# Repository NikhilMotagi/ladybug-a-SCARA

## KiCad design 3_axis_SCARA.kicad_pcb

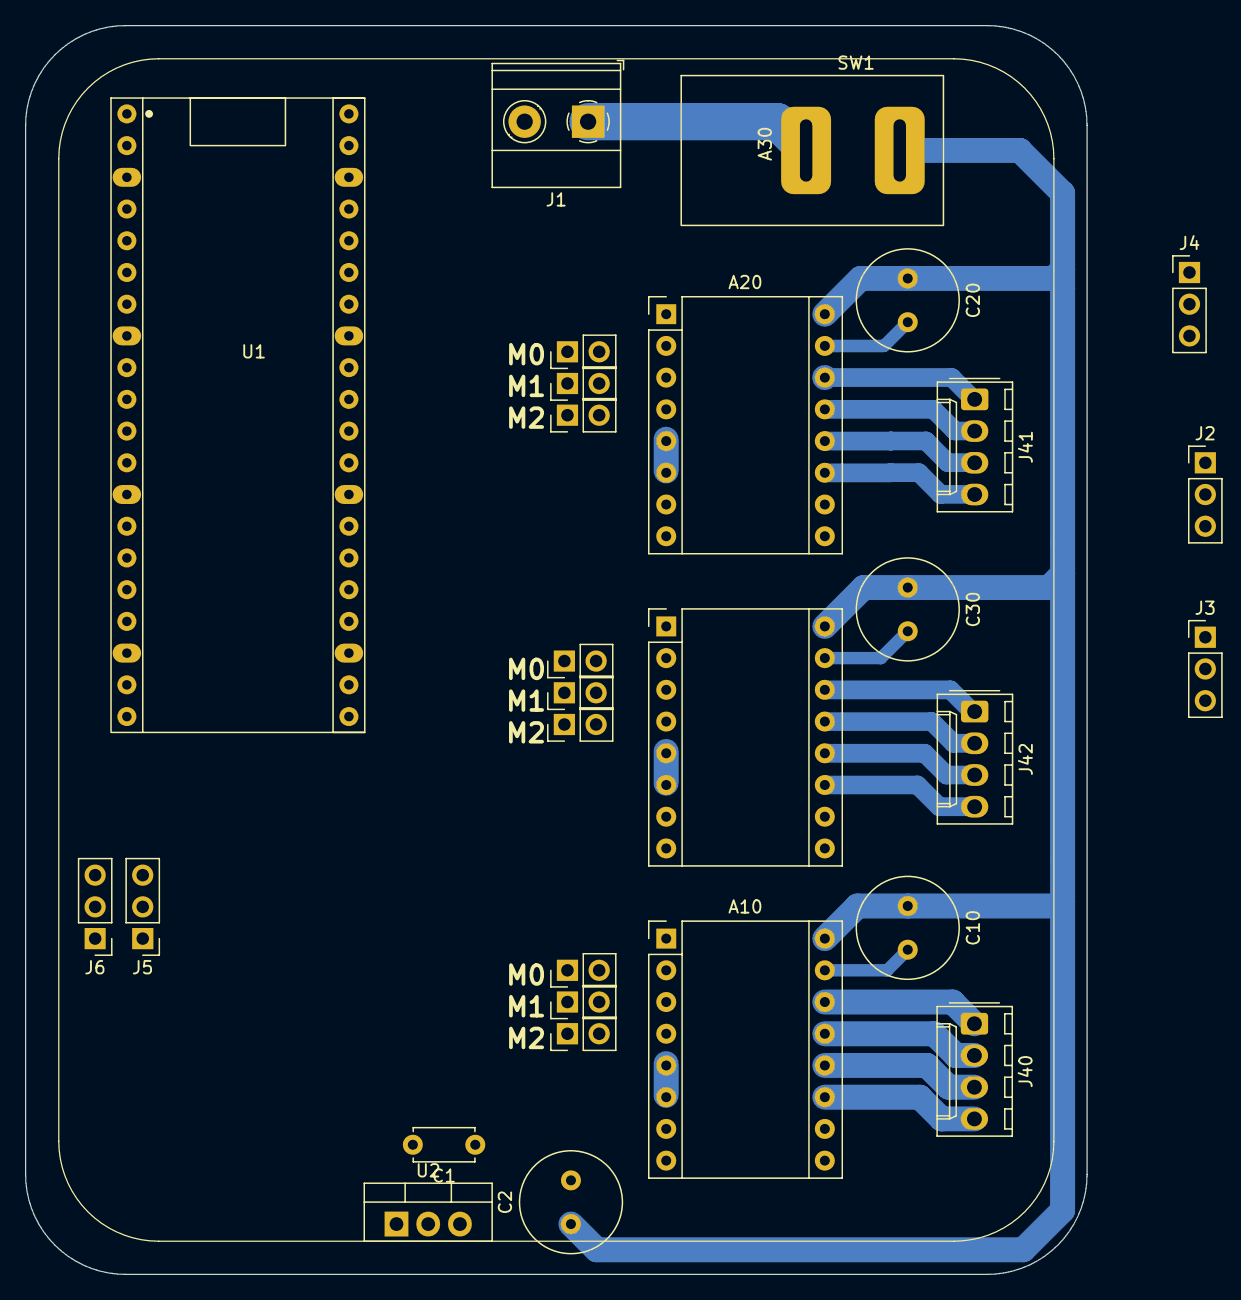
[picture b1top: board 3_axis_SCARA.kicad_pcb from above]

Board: 2 copper layers, 85.0 x 100.0 mm, 29 parts (0 on the bottom side), 29 nets.

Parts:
A10, A20, A30: Breakout_DRV8825; Pololu_Breakout-16_15.2x20.3mm
C1: C; C_Disc_D4.7mm_W2.5mm_P5.00mm
C2, C10, C20, C30: C_Polarized; C_Radial_D8.0mm_H11.5mm_P3.50mm
J1: Screw_Terminal; TerminalBlock_Phoenix_MKDS-1,5-2-5.08_1x02_P5.08mm_Horizont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
J2: Servo_1; PinHeader_1x03_P2.54mm_Vertical
J3: Servo_2; PinHeader_1x03_P2.54mm_Vertical
J4: Base_Z; PinHeader_1x03_P2.54mm_Vertical
J5: Arm_1; PinHeader_1x03_P2.54mm_Vertical
J6: Arm_2; PinHeader_1x03_P2.54mm_Vertical
J10: M0_A1; PinHeader_1x02_P2.54mm_Vertical
J11: M1_A1; PinHeader_1x02_P2.54mm_Vertical
J12: M2_A1; PinHeader_1x02_P2.54mm_Vertical
J20: M0_A2; PinHeader_1x02_P2.54mm_Vertical
J21: M1_A2; PinHeader_1x02_P2.54mm_Vertical
J22: M2_A2; PinHeader_1x02_P2.54mm_Vertical
J30: M0_A3; PinHeader_1x02_P2.54mm_Vertical
J31: M1_A3; PinHeader_1x02_P2.54mm_Vertical
J32: M2_A3; PinHeader_1x02_P2.54mm_Vertical
J40: S1_conn; Molex_KK-254_AE-6410-04A_1x04_P2.54mm_Vertical
J41: S2_conn; Molex_KK-254_AE-6410-04A_1x04_P2.54mm_Vertical
J42: S3_conn; Molex_KK-254_AE-6410-04A_1x04_P2.54mm_Vertical
SW1: SW_SPST; DPDT_SW
U1: Raspberry PICO W; Raspberry_pico_w
U2: LM7805_TO220; TO-220-3_Vertical

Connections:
+5V: A10.5 (~RST), A10.6 (~SLP), A20.5 (~RST), A20.6 (~SLP), A30.5 (~RST), A30.6 (~SLP), C1.1, J2.1, J3.1, J4.1, J5.1, J6.1, J10.1, J11.1, J12.1, J20.1, J21.1, J22.1, J30.1, J31.1, J32.1, U1.40 (VBUS), U2.3 (VO)
+24V: A10.16 (VMOT), A20.16 (VMOT), A30.16 (VMOT), C2.1, C10.1, C20.1, C30.1, SW1.2 (B), U2.1 (VI)
/A10_M0: A10.2 (M0), J10.2
/A10_M1: A10.3 (M1), J11.2
/A10_M2: A10.4 (M2), J12.2
/A20_M0: A20.2 (M0), J20.2
/A20_M1: A20.3 (M1), J21.2
/A20_M2: A20.4 (M2), J22.2
/A30_M0: A30.2 (M0), J30.2
/A30_M1: A30.3 (M1), J31.2
/A30_M2: A30.4 (M2), J32.2
/ADC0: J6.2, U1.31 ((ADC0)_GP26)
/ADC1: J5.2, U1.32 ((ADC1)_GP27)
/ADC2: J4.2, U1.34 ((ADC2)_GP28)
/GP18: U1.21 (GP16), U1.24 (GP18)
/S1_A1: A10.12 (A1), J40.3
/S1_A2: A10.11 (A2), J40.4
/S1_B1: A10.13 (B1), J40.2
/S1_B2: A10.14 (B2), J40.1
/S2_A1: A20.12 (A1), J41.3
/S2_A2: A20.11 (A2), J41.4
/S2_B1: A20.13 (B1), J41.2
/S2_B2: A20.14 (B2), J41.1
/S3_A1: A30.12 (A1), J42.3
/S3_A2: A30.11 (A2), J42.4
/S3_B1: A30.13 (B1), J42.2
/S3_B2: A30.14 (B2), J42.1
GND: A10.9 (GND), A10.15 (GND), A20.9 (GND), A20.15 (GND), A30.9 (GND), A30.15 (GND), C1.2, C2.2, C10.2, C20.2, C30.2, J1.2, J2.3, J3.3, J4.3, J5.3, J6.3, U1.3 (GND), U1.8 (GND), U1.13 (GND), U1.18 (GND), U1.23 (GND), U1.28 (GND), U1.33 ((AGND)_GND), U1.38 (GND), U2.2 (GND)
unnamed: J1.1, SW1.1 (A)

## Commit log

2023-05-22 pcb repo
